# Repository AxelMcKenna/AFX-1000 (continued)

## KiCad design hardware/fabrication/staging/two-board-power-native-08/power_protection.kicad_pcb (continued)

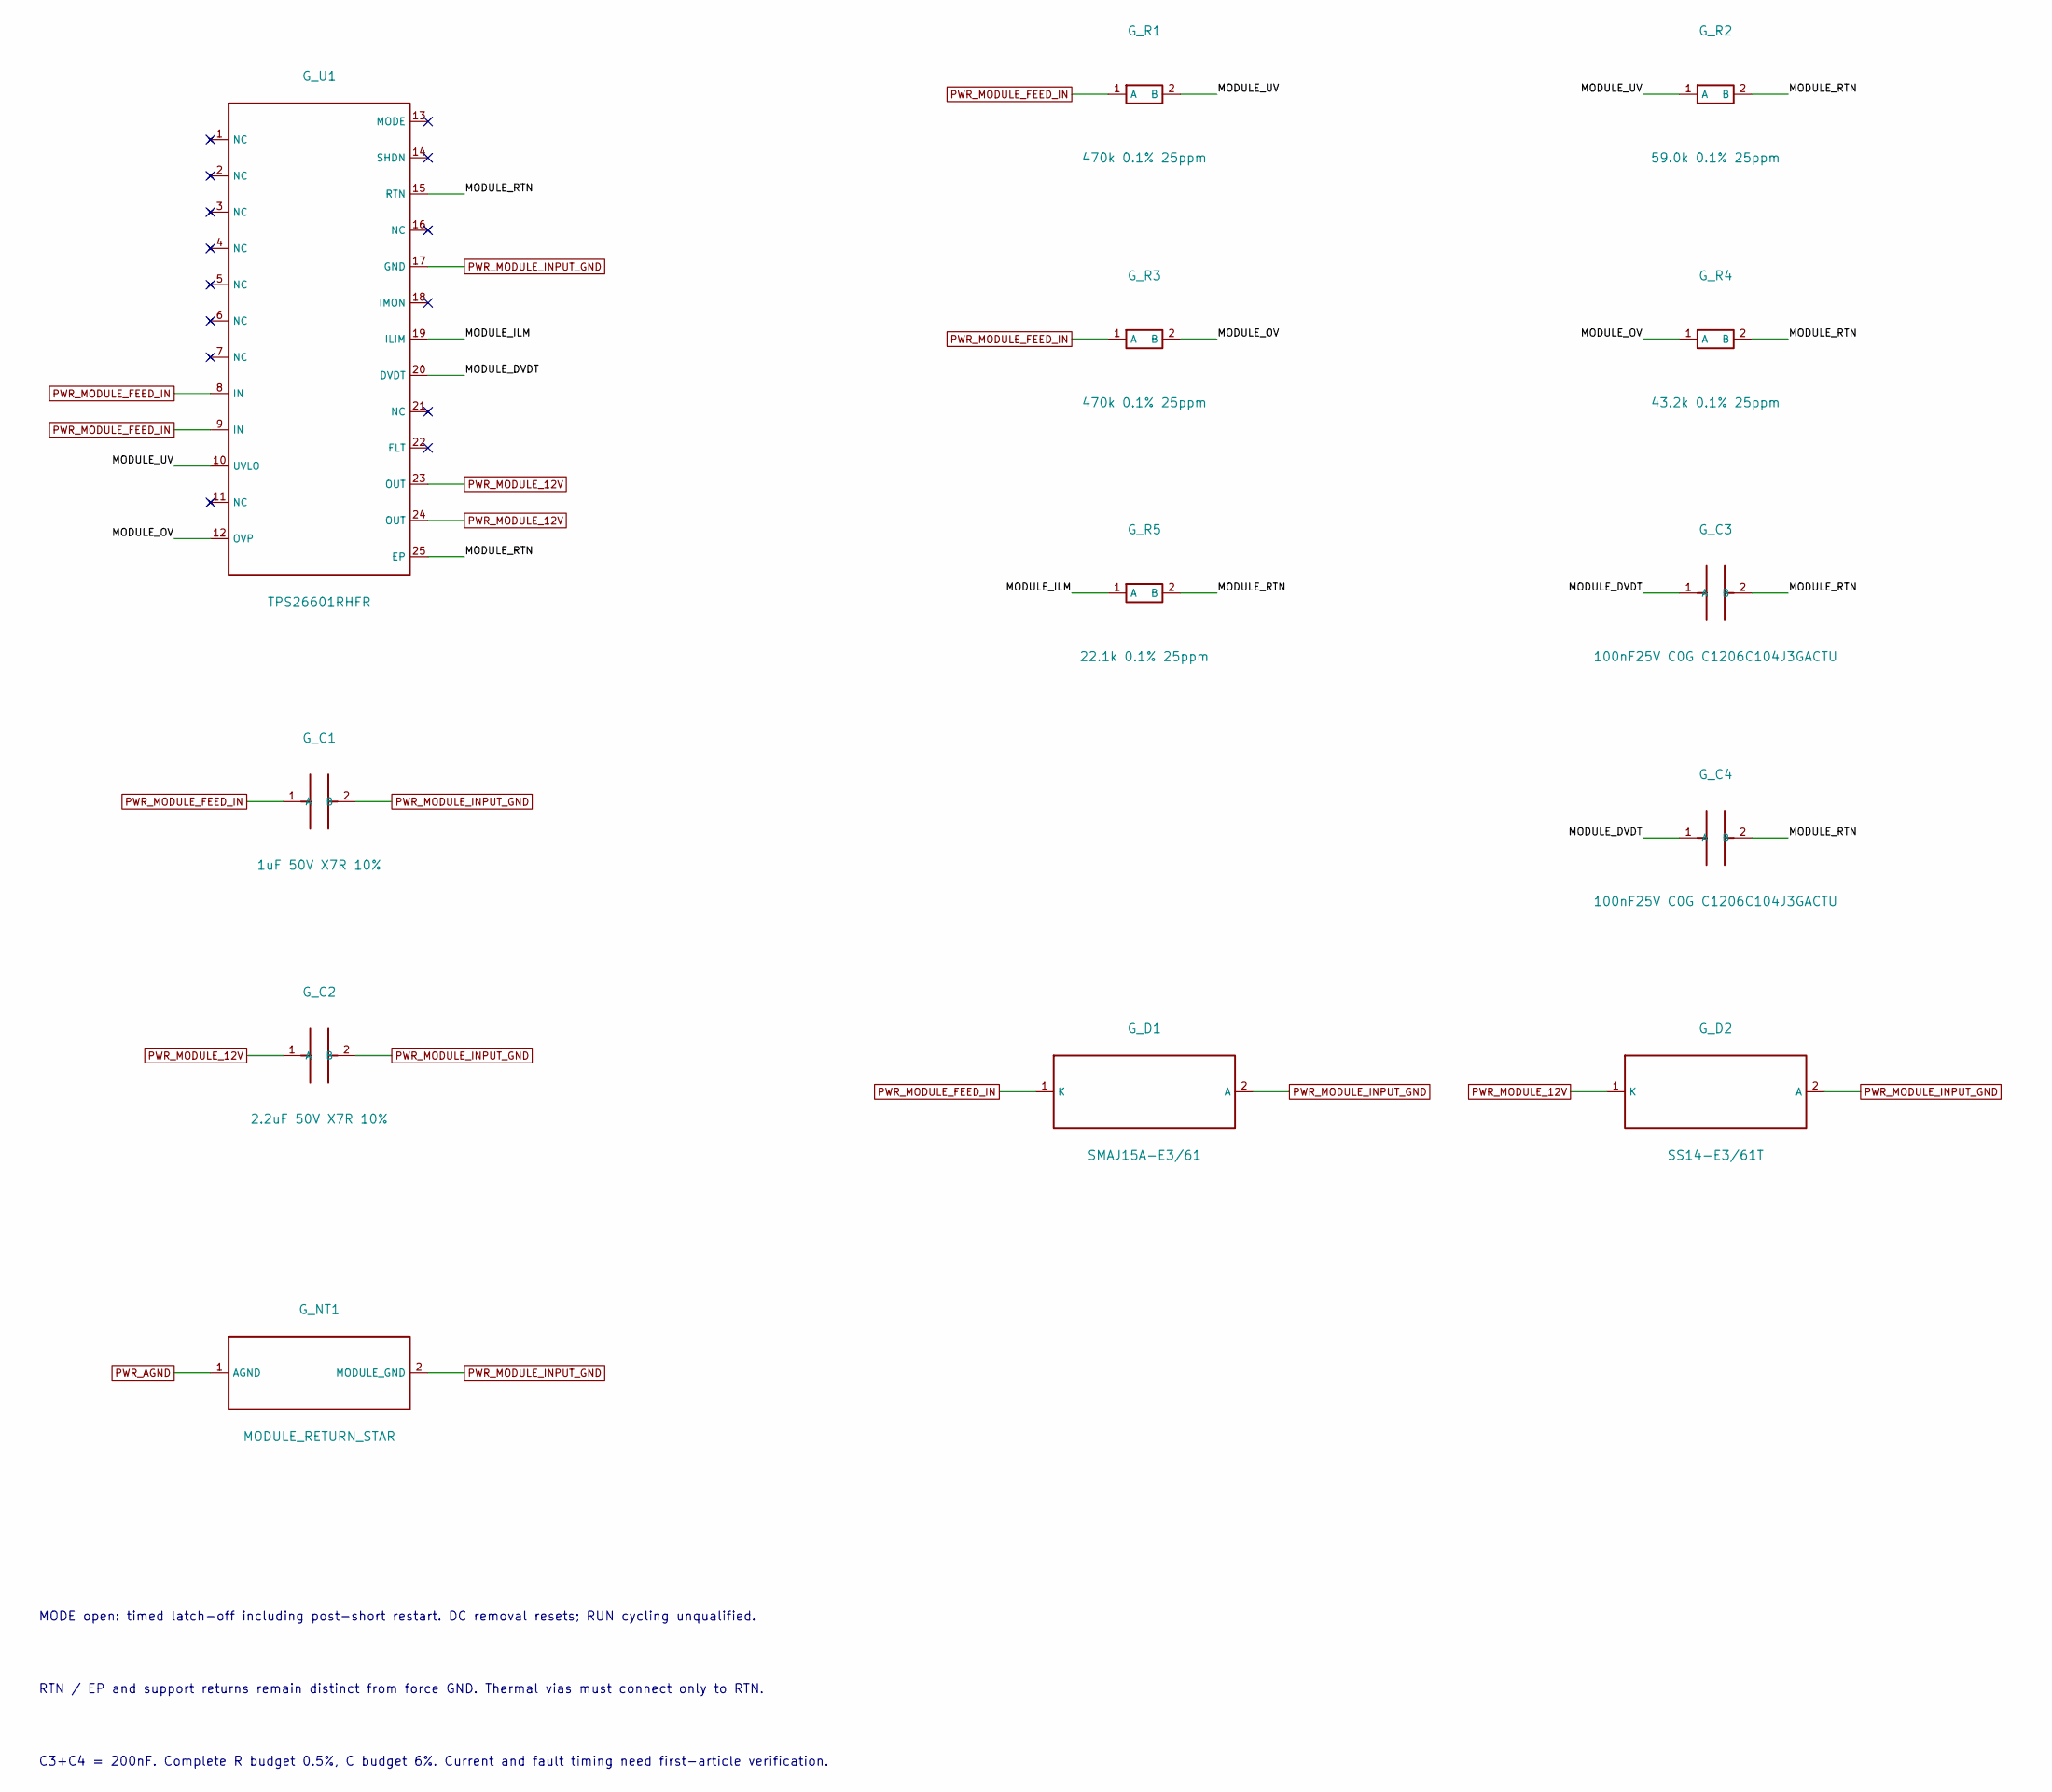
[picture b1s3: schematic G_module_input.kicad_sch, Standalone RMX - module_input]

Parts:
G_C1: 1uF 50V X7R 10%; C_0805_2012Metric
G_C2: 2.2uF 50V X7R 10%; C_1206_3216Metric
G_C3, G_C4: 100nF25V C0G C1206C104J3GACTU; PROPOSED_KEMET1206_LevelB
G_D1: SMAJ15A-E3/61; D_SMA
G_D2: SS14-E3/61T; D_SMA
G_NT1: MODULE_RETURN_STAR; Return_Star
G_R1, G_R3: 470k 0.1% 25ppm; R_0603_1608Metric
G_R2: 59.0k 0.1% 25ppm; R_0603_1608Metric
G_R4: 43.2k 0.1% 25ppm; R_0603_1608Metric
G_R5: 22.1k 0.1% 25ppm; R_0603_1608Metric
G_U1: TPS26601RHFR; TI_RHF0024A

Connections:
/G_module_input/MODULE_OV: G_R3.2 (B), G_R4.1 (A), G_U1.2 (NC), G_U1.12 (OVP)
PWR_AGND: G_NT1.1 (AGND); also elsewhere on the board
PWR_MODULE_12V: G_C2.1 (A), G_D2.1 (K), G_U1.6 (NC), G_U1.23 (OUT), G_U1.24 (OUT); also elsewhere on the board

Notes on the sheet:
MODE open: timed latch-off including post-short restart. DC removal resets; RUN cycling unqualified.
RTN / EP and support returns remain distinct from force GND. Thermal vias must connect only to RTN.
C3+C4 = 200nF. Complete R budget 0.5%, C budget 6%. Current and fault timing need first-article verification.

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
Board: 8 copper layers, 1105 parts (410 on the bottom side), 635 nets, no tracks yet.

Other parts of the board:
H_NEW1: PROPOSED_NPTH; H_NEW1
H_NEW2: PROPOSED_NPTH; H_NEW2
H_NEW3: PROPOSED_NPTH; H_NEW3
H_NEW4: PROPOSED_NPTH; H_NEW4
H_NEW5: PROPOSED_NPTH; H_NEW5
H_NEW6: PROPOSED_NPTH; H_NEW6
H_NEW7: PROPOSED_NPTH; H_NEW7
H_NEW8: PROPOSED_NPTH; H_NEW8
H_NEW9: PROPOSED_NPTH; H_NEW9
H_NEW10: PROPOSED_NPTH; H_NEW10
H_NEW11: PROPOSED_NPTH; H_NEW11
H_TOUCH1: PROPOSED_NPTH; H_TOUCH1
H_TOUCH2: PROPOSED_NPTH; H_TOUCH2
I_J2: B2PS-VH(LF)(SN); JST_VH_B2PS-VH_1x02_P3.96mm_Horizontal
N_H101, N_H102: STRAIN_POST_2p6_NPTH_RECEIVING
P_J101: JST B2PS-VH (VHR-2N/SVH-41T-P1.1 AWG16); JST_VH_B2PS-VH_1x02_P3.96mm_Horizontal

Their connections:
PWR_AGND: I_J2.2, P_J101.2; also elsewhere on the board
PWR_DC_IN: I_J2.1, P_J101.1; also elsewhere on the board
